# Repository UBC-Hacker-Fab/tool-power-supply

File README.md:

# Tool power supply

A general-purpose power supply board for HackerFab tools. Rev 1 targets the **spin coater** (A2212 930KV BLDC through an EMAX ESC) and the **tube furnace** (up to about 1000 W, switched by an off-board Fotek SSR-60 DA), and also gives general 12 V / 5 V / 3.3 V taps for future tools. A Raspberry Pi Pico 2 monitors and controls it.

Status: **rev 1 schematic done, PCB layout restarted at 90 x 160 mm (120 x 80 mm did not fit); a placement is in the project PCB (first pass scripted, see `tools/pcb_placement/`; the CAN, expander, M3 hole and XT60 changes were laid out by a targeted update on 2026-10-24 that keeps the hand edits; the layout was then finished by hand on 2026-10-25) and routed on 2026-10-26 (hand-planned scripts, no autorouter; KiCad DRC: 0 unconnected, 0 parity issues, only silkscreen items left).** Nothing has been fabricated. Several numbers (creepage, thermal, ESC behavior) are from memory or summaries and are flagged as unverified in the design docs; check them before ordering boards.

Spec source: the Notion page "Power Board Spec Sheet" (HackerFab Central / Electrical): https://app.notion.com/p/38d37907206980e6a0a9c241ee033941. Fab and assembly are planned through JLC (LCSC part numbers in the BOM); through-hole parts are hand-soldered and can come from Digikey or Mouser.

## What the board does

- **120 VAC in** (barrier strip, L / N / PE) splits into two fused branches: a 3 A time-lag branch into the on-board **Mean Well IRM-90-12** (12 V, 6.7 A, 80 W), and a 10 A fast-blow branch through an ACS712 current sensor to the **AC out** barrier strip. An external SSR in the heater's hot lead switches the furnace.
- **12 V bus** (module output) with a 5 mOhm INA226 monitor, an SMCJ15A TVS and a 100 uF bulk cap. There is **no 24 V bus** and no diode between the module and the bus.
- **12 V outputs:** two taps (3 A blade fuse each) and the ESC branch (7.5 A blade fuse, XT60 female). Each is a fuse, then a high-side AO4407C P-FET switch.
- **5 V and 3.3 V rails:** AP63205 and AP63203 fixed bucks off the 12 V bus, each with an INA226 monitor, then two TPS2553 current-limited taps per rail.
- **Pico 2** plugs into sockets. It reads the three INA226s over I2C, switches every DC tap (default ON, pulled low to turn off), senses whether each tap output is present, reads furnace current and two NTCs, drives the SSR through a 2N7002, and drives a 4-pin PWM fan header. The logic-level SMD parts (expander, sense dividers, pull-ups, SSR drive, VSYS diode) sit on the top side in the pocket under the Pico, between the two 8.5 mm sockets. The Pico 2 ships without headers, so it needs two 1x20 male headers (not yet in the BOM).
- **Power budget:** sized for **one tool at a time** (spin coater worst case about 70 W). It is not enforced in hardware, so the 6.7 A limit should be labeled on the board.

Out of scope for rev 1: the litho tool (it keeps its own supplies), the ESC throttle signal (a separate microcontroller handles it), and the thermocouple interface.

## Repository map

| Path | What it is |
|---|---|
| `design-context/design-decisions.md` | Working memory: every decision with its rationale, open questions, datasheet-derived numbers and sourcing. Start here for "why is it like this". |
| `design-context/bom.md` | Rev 1 BOM (LCSC / Digikey / Mouser part numbers, quantities, JLC vs hand assembly). |
| `design-context/routing.md` | How the board is routed: presets, layer plan, lane bundles, placement changes made for routing, checks and results. |
| `design-context/pin-map.md` | Pico 2 GPIO assignment, tap sense circuits, 12 V switch circuit, INA226 addresses. |
| `design-context/power-tree.md` | Generated power tree with consumption per rail and per tap, module budget by scenario. Regenerate with `python3 tools/power_tree/gen_power_tree.py`. |
| `design-context/block-diagram.svg` | Block diagram (Graphviz source `block-diagram.dot`; Mermaid version in `block-diagram.md`). |
| `design-context/pcb-placement.md` | Board outline, zone plan and placement assumptions for the first-pass PCB. |
| `design-context/footprint-sourcing.md` | Which symbols and footprints come from stock KiCad, the HackerFab library, or need downloading. |
| `tool-power-supply-v1/` | The KiCad 10 project: root sheet plus `mains`, `bus12v`, `rails`, `mcu` sub-sheets. |
| `tools/power_tree/` | Generator for `power-tree.md`: reads the schematic through the kicad-happy `kicad` skill and `power_model.json` (off-board loads and assumptions, each with a source). |
| `tools/routing/` | Hand-planned PCB routing scripts, checker and DRC loop (see its README). |
| `tools/schematic/` | Python generator that wrote the schematic (see "Working on the schematic"). |
| `datasheets/` | Datasheets referenced by the decisions (INA226, TPS2553, ACS712, Pico 2, EMAX ESC, and rejected parts). |

## Reviewing the design

1. Read the block diagram above, then the "Decided" sections of `design-context/design-decisions.md`.
2. Open `tool-power-supply-v1/tool-power-supply-v1.kicad_pro` in **KiCad 10**. The schematic is hierarchical: the root sheet shows four sheet symbols joined by sheet pins and bus groups (`I2C`, `EN`, `SENSE`, `FAULT`, `FAN`), and the sheets are wired functional blocks with power symbols and no global labels.
3. Symbols and footprints come from the stock KiCad libraries plus the HackerFab libraries (`hackerfab-kicadlibs`, https://github.com/UBC-Hacker-Fab). A few parts (TPS2553, the 3AG and blade fuses with their clip/holder footprints, barrier strip, IRM-90-12) are only in the HackerFab library, so clone that repo and add its libraries to KiCad before opening the project.
4. Check the BOM (`design-context/bom.md`) against the schematic and pin map.

Current check results: ERC has 0 errors and 2 expected warnings (the Pico's GND and AGND power-output pins tied to the module's -VO pin). The exported netlist matches the intended pin-to-net table for all 79 nets.

**2026-10-26: Pico GPIO re-pinned for routing** (`design-context/pin-map.md`): the left socket order now matches the order the nets leave toward U8 to U11, Q4 to Q6, U14 and the I2C / fan group, and the seven EN pull-ups sit beside their pins. Edited in `mcu.kicad_sch` and the PCB pad nets only; ERC result is unchanged by the change (it currently lists 4 items: the U12 ~{INT} pin and its misplaced no-connect flag, and the Pico GND / AGND pin-type warnings). `tools/schematic/design.py` still has the old pin map.

## Known gaps and open items

- **PCB: routed 2026-10-26, not yet reviewed in KiCad** (90 x 160 mm, 4-layer JLC economy stack-up: F.Cu / In1 GND / In2 GND / B.Cu; routing method, presets, bundles and checks in `design-context/routing.md`, scripts in `tools/routing/`). Four GND pours (stitched, filled with the DRC engine so the 3.2 mm mains rule holds), 612 tracks, 466 vias; DRC with the project's net classes and schematic parity: 0 unconnected, no clearance / hole / mains violations, 164 silkscreen warnings (silk left for later) and the known U13 footprint-library note. Placement was adjusted a little for routing (Q5, the divider resistors, R36 / R37, the EN pull-ups, F4 / F5 flipped; list in `design-context/routing.md`). Placement history: `design-context/pcb-placement.md` and `tools/pcb_placement/`. Still open on the layout: creepage slots (under the IRM-90-12, around the ACS712 and the mains LED dropper), the star-ground solder jumpers (PE, DC GND, ESC, logic, chassis; default open), silkscreen, and a check of the tight vias (0.5 / 0.3 mm) against the JLC DFM report.
- **Schematic omissions:** X2 cap, test points, a gate clamp for the 12 V P-FETs (check Vgs against the 25 V limit during a TVS clamp), and the AO4407C uses the stock FDS9435A symbol. The 120 VAC 3AG fuses (F1, F2) are one symbol each with a custom two-clip footprint (34.21 mm between the clips, from the Littelfuse datasheet); the DC blade fuses (F4, F5, F6) are one symbol each with the Keystone 3557 holder as the footprint, so there are no separate clip or holder symbols.
- **Unverified assumptions:** the ESC's regen behavior (the IRM-90-12 latches off above 12.6 to 16.2 V and needs a power cycle; the design relies on ESC Brake OFF and a ramped throttle), the ESC's own input capacitance (the 100 uF bulk cap assumes the ESC has some), the Fotek SSR's real ratings, creepage numbers (now derived from IEC 60664-1 in `design-guides/`, still to be confirmed), and the Noctua fan's PWM and tach levels. The EMAX manual in `datasheets/` is for the NANO series, not the Simon series in use.
- **Decided 2026-10-21 (design review); in the schematic since 2026-10-22 and in the PCB (placement only) since 2026-10-24:** the board becomes a CAN peripheral of the control board (a second Pico 2 on USB to a lab computer, powered from this board's 5 V). The Pico 2 stays and uses the can2040 PIO CAN library with an SN65HVD230 transceiver; a TCA9534 8-bit I2C expander takes the 7 sense inputs (25 of 26 GPIO becomes 20); mounting holes become floating M3 plated holes with ring vias; the ESC XT60 becomes a vertical female (XT60PB-F, C19268038). New parts: U12 TCA9534PWR (C783615; first drawn as a 16-bit PCA9535C, swapped by the user 2026-10-24 because only 8 inputs are used), U14 SN65HVD230, J10 link connector (5 V, CANH, GND, CANL; replaces J9), R41 + SJ4 termination. Future note: the control board should fall back to USB power if the power board fails. Details in `design-context/design-decisions.md`.
- **Not yet sourced:** M2 hardware and standoffs, the SSR heat sink and wiring, and the DNP dump-load footprint.
- Prices and stock figures date from 2026-10-11 to 2026-10-14. Re-check before ordering.

## Working on the schematic

The schematic was generated from Python tables, and `tools/schematic/design.py` is the source of truth for components and nets.

```sh
python3 tools/schematic/build2.py   # regenerate tool-power-supply-v1/*.kicad_sch
```

It needs KiCad 10 installed at `/Applications/KiCad/KiCad.app` and `hackerfab-kicadlibs` cloned at `~/Documents/Github/hackerfab-kicadlibs`. **Regenerating overwrites any edits made in KiCad.** The schematic is now being edited by hand, so do not rerun the generator unless you have agreed to throw those edits away (it refuses to run while KiCad's `~*.lck` file exists); `design.py` can drift from the `.kicad_sch` files. `tools/schematic/README.md` has details.

## Power tree

`design-context/power-tree.md` is generated from the schematic, so rerun `python3 tools/power_tree/gen_power_tree.py` after any schematic or load change (`--check` reports whether the committed file is stale). It needs Python 3.10+ and the kicad-happy `kicad` skill (default `~/.claude/skills/kicad`, override with `KICAD_HAPPY_SKILL`). Tap and overhead currents live in `tools/power_tree/power_model.json`; the generator fails if a ref in that file no longer matches the schematic. Headline result today: the spin-coater case draws about 5.9 A of the module's 6.7 A, and loading every tap at once exceeds the module, as expected for a one-tool-at-a-time design.

## Keeping this README current

This file is the first point of contact, so it must match the design. When a decision, the architecture, the BOM, the schematic status or the open items change, update the relevant section here in the same change, alongside `design-context/design-decisions.md` (which holds the detail and history).

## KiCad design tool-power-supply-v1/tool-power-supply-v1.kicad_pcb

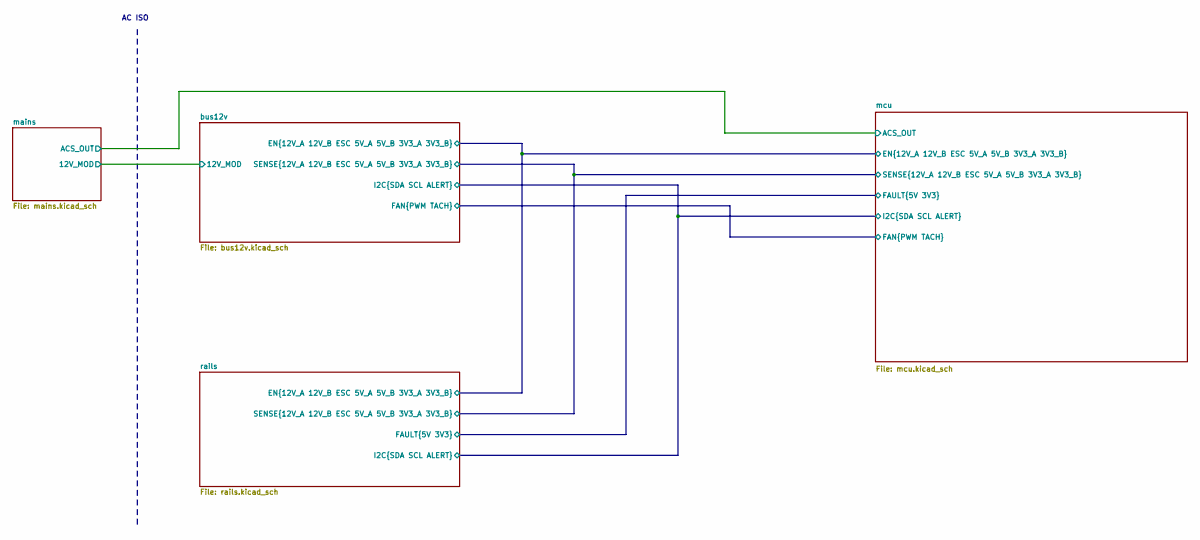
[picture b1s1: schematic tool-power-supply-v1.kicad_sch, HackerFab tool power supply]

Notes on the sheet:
AC ISO

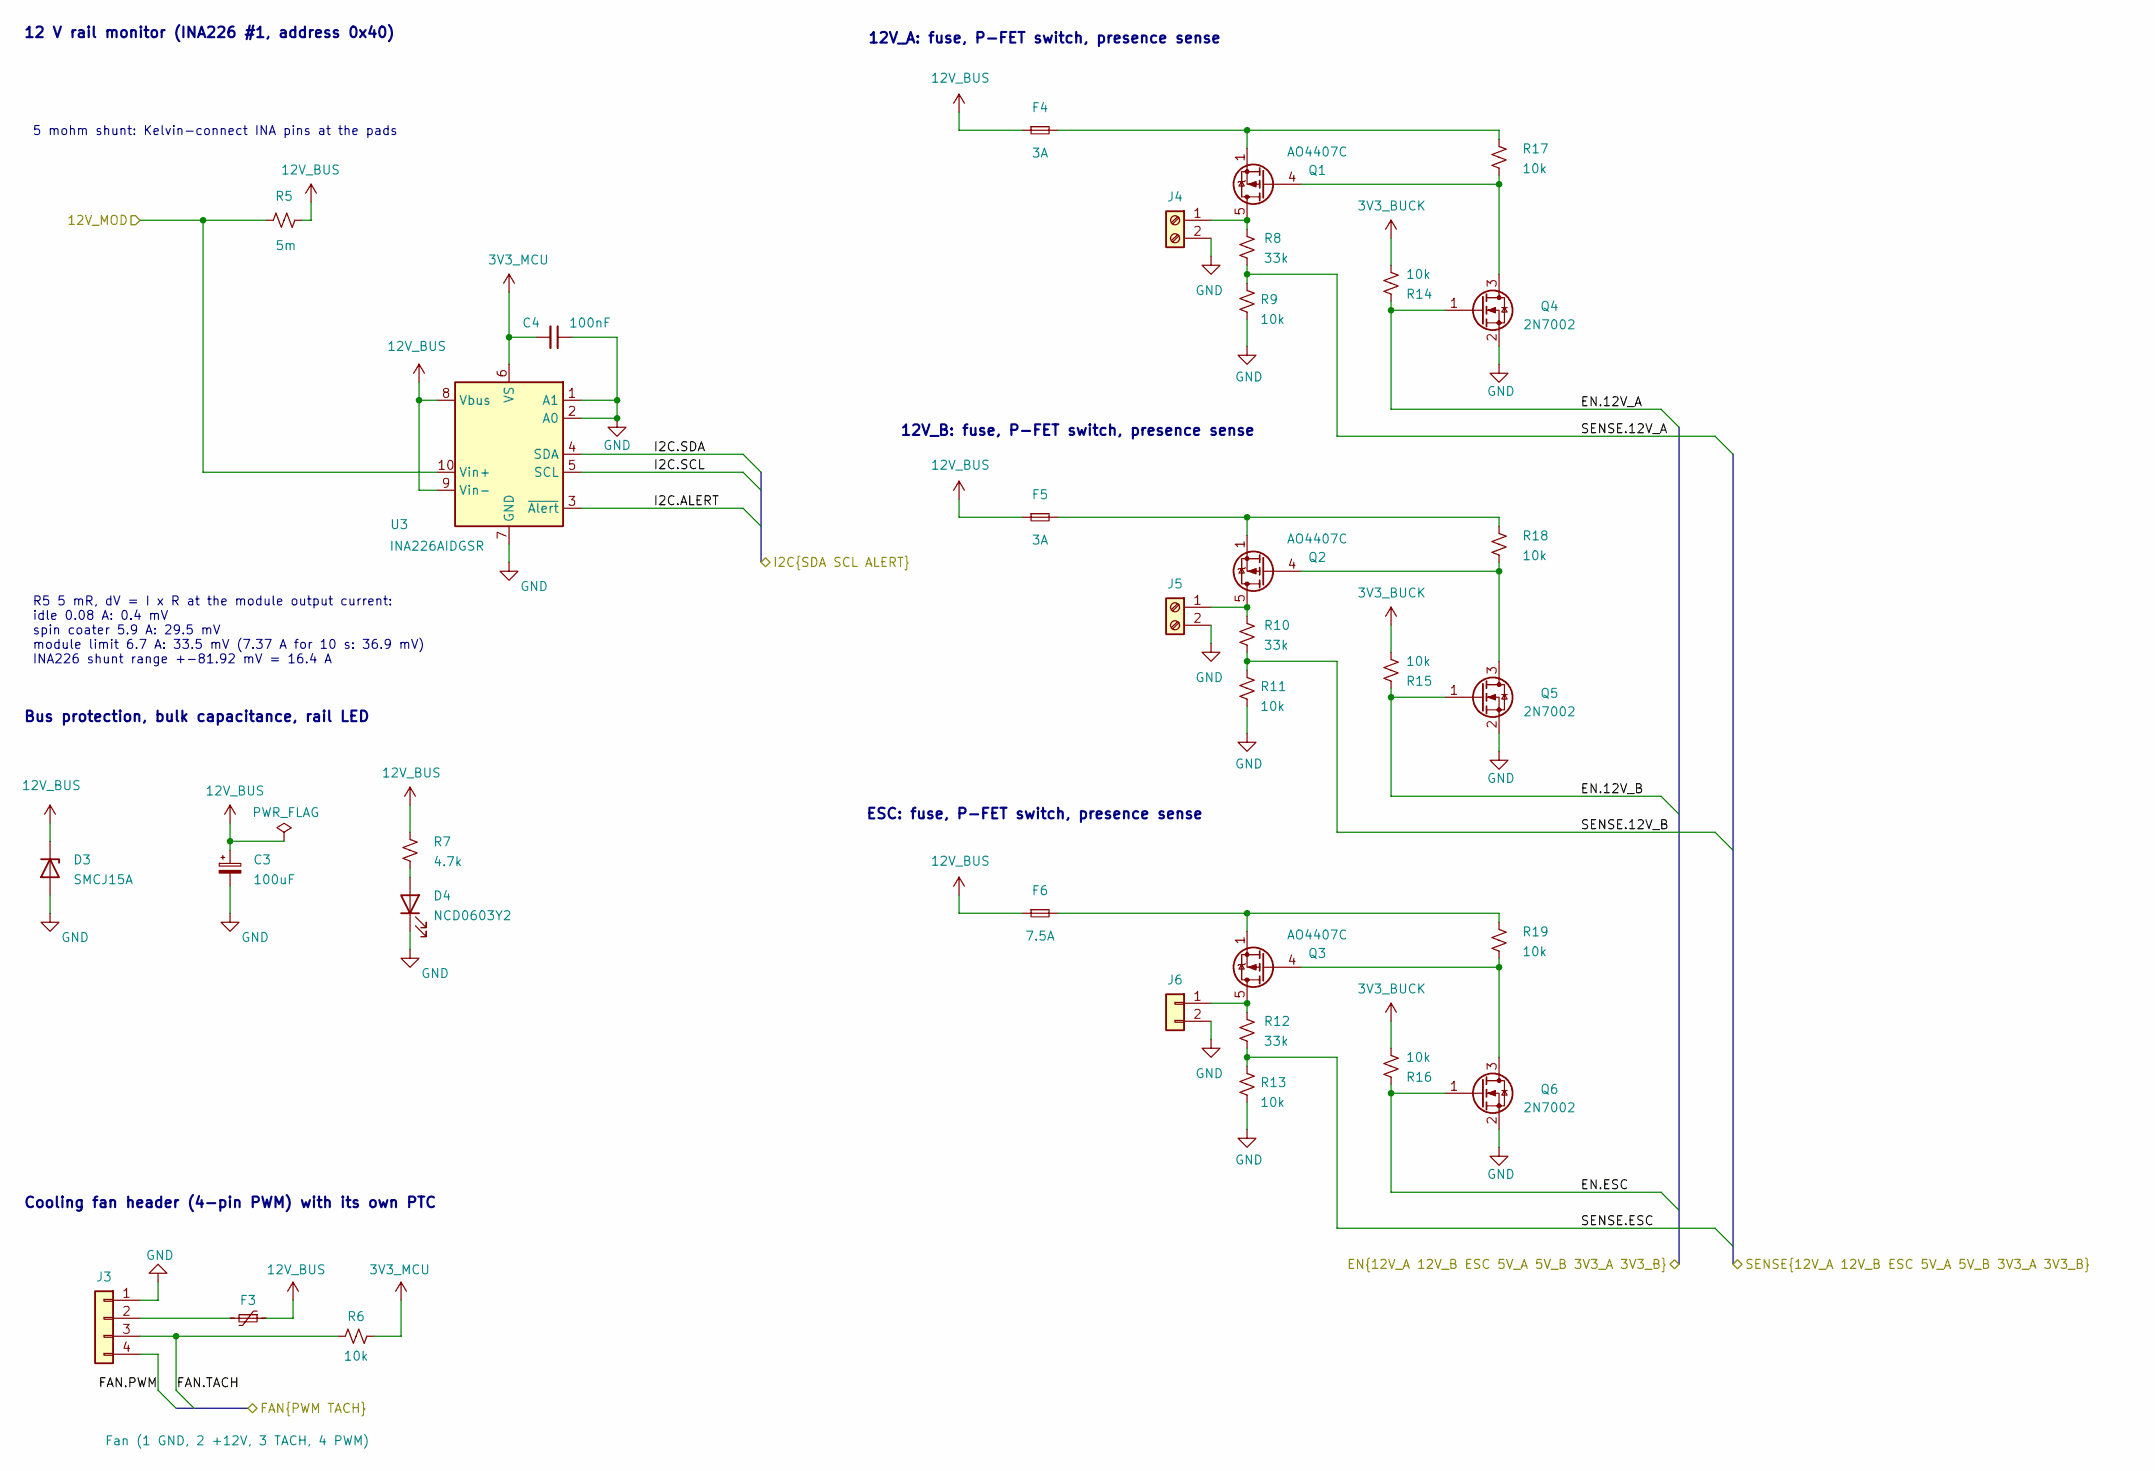
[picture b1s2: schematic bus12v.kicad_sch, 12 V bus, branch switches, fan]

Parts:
C3: 100uF; CP_Elec_6.3x7.7; Voltage 35V; MPN RVE100UF35V67RV0072; LCSC C2836437
C4: 100nF; C_0603_1608Metric; Voltage 50V; MPN CC0603KRX7R9BB104; LCSC C14663
D3: SMCJ15A; D_SMC; MPN SMCJ15A; LCSC C42371550
D4: NCD0603Y2; LED_0603_1608Metric; MPN NCD0603Y2; LCSC C89811
F3: 500mA; Fuse_1206_3216Metric; MPN nSMD050-33V; LCSC C70077
F4, F5: 3A; Fuse_Blade_Keystone_3557-20_P13.47mm; MPN 0ATO003.V (Digikey F5040-ND)
F6: 7.5A; Fuse_Blade_Keystone_3557-20_P13.47mm; MPN 0ATO07.5V (Digikey F11167-ND)
J3: Fan (1 GND, 2 +12V, 3 TACH, 4 PWM); Molex_KK-254_AE-6410-04A_1x04_P2.54mm_Vertical; MPN 47053-1000; Mouser 538-47053-1000
J4, J5: DB128V-5.08-2P-GN-S; TerminalBlock_CUI_TB007-508-02_1x02_P5.08mm_Horizontal; MPN DB128V-5.08-2P-GN-S; LCSC C2915639
J6: XT60PW-F; AMASS_XT60PW-F_1x02_P7.20mm_Horizontal; MPN XT60PW-F; LCSC C428722
Q1, Q2, Q3: AO4407C; SOIC-8_3.9x4.9mm_P1.27mm; MPN AO4407C; LCSC C469397
Q4, Q5, Q6: 2N7002; SOT-23; MPN 2N7002; LCSC C8545
R5: 5m; R_2512_6332Metric; Tolerance 1%; MPN RLP25FEGMR005; LCSC C393074
R6, R9, R11, R13, R14, R15, R16, R17, R18, R19: 10k; R_0603_1608Metric; Tolerance 1%; MPN 0603WAF1002T5E; LCSC C25804
R7: 4.7k; R_0603_1608Metric; Tolerance 1%; MPN 0603WAF4701T5E; LCSC C23162
R8, R10, R12: 33k; R_0603_1608Metric; Tolerance 1%; MPN 0603WAF3302T5E; LCSC C4216
U3: INA226AIDGSR; MSOP-10_3x3mm_P0.5mm; MPN INA226AIDGSR; LCSC C49851

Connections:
3V3_MCU: C4.1, R6.2, U3.6 (VS); also elsewhere on the board
12V_BUS: C3.1, D3.1 (K), F3.1, F4.1, F5.1, F6.1, R5.2, R7.1, U3.8 (Vbus), U3.9 (Vin-); also elsewhere on the board
/bus12v/12V_MOD: R5.1, U3.10 (Vin+); also elsewhere on the board
/bus12v/EN.12V_A: Q4.1 (G), R14.1; also elsewhere on the board
/bus12v/EN.12V_B: Q5.1 (G), R15.1; also elsewhere on the board
/bus12v/EN.ESC: Q6.1 (G), R16.1; also elsewhere on the board
/bus12v/FAN.PWM: J3.4; also elsewhere on the board
/bus12v/FAN.TACH: J3.3, R6.1; also elsewhere on the board
/bus12v/I2C.ALERT: U3.3 (~Alert); also elsewhere on the board
/bus12v/I2C.SCL: U3.5 (SCL); also elsewhere on the board
/bus12v/I2C.SDA: U3.4 (SDA); also elsewhere on the board
/bus12v/SENSE.12V_A: R8.2, R9.1; also elsewhere on the board
/bus12v/SENSE.12V_B: R10.2, R11.1; also elsewhere on the board
/bus12v/SENSE.ESC: R12.2, R13.1; also elsewhere on the board
GND: C3.2, C4.2, D3.2 (A), D4.1 (K), J3.1, J4.2, J5.2, J6.2 (-), Q4.2 (S), Q5.2 (S), Q6.2 (S), R9.2, R11.2, R13.2, U3.1 (A1), U3.2 (A0), U3.7 (GND); also elsewhere on the board
unnamed: D4.2 (A), R7.2
unnamed: F4.2, Q1.1 (S), Q1.2 (S), Q1.3 (S), R17.1
unnamed: F5.2, Q2.1 (S), Q2.2 (S), Q2.3 (S), R18.1
unnamed: F6.2, Q3.1 (S), Q3.2 (S), Q3.3 (S), R19.1
unnamed: F3.2, J3.2
unnamed: J4.1, Q1.5 (D), Q1.6 (D), Q1.7 (D), Q1.8 (D), R8.1
unnamed: J5.1, Q2.5 (D), Q2.6 (D), Q2.7 (D), Q2.8 (D), R10.1
unnamed: J6.1 (+), Q3.5 (D), Q3.6 (D), Q3.7 (D), Q3.8 (D), R12.1
unnamed: Q1.4 (G), Q4.3 (D), R17.2
unnamed: Q2.4 (G), Q5.3 (D), R18.2
unnamed: Q3.4 (G), Q6.3 (D), R19.2

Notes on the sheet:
ESC: fuse, P-FET switch, presence sense
Cooling fan header (4-pin PWM) with its own PTC
Bus protection, bulk capacitance, rail LED
12 V rail monitor (INA226 #1, address 0x40)
12V_A: fuse, P-FET switch, presence sense
R5 5 mR, dV = I x R at the module output current: idle 0.08 A: 0.4 mV spin coater 5.9 A: 29.5 mV module limit 6.7 A: 33.5 mV (7.37 A for 10 s: 36.9 mV) INA226 shunt range +-81.92 mV = 16.4 A
5 mohm shunt: Kelvin-connect INA pins at the pads
12V_B: fuse, P-FET switch, presence sense

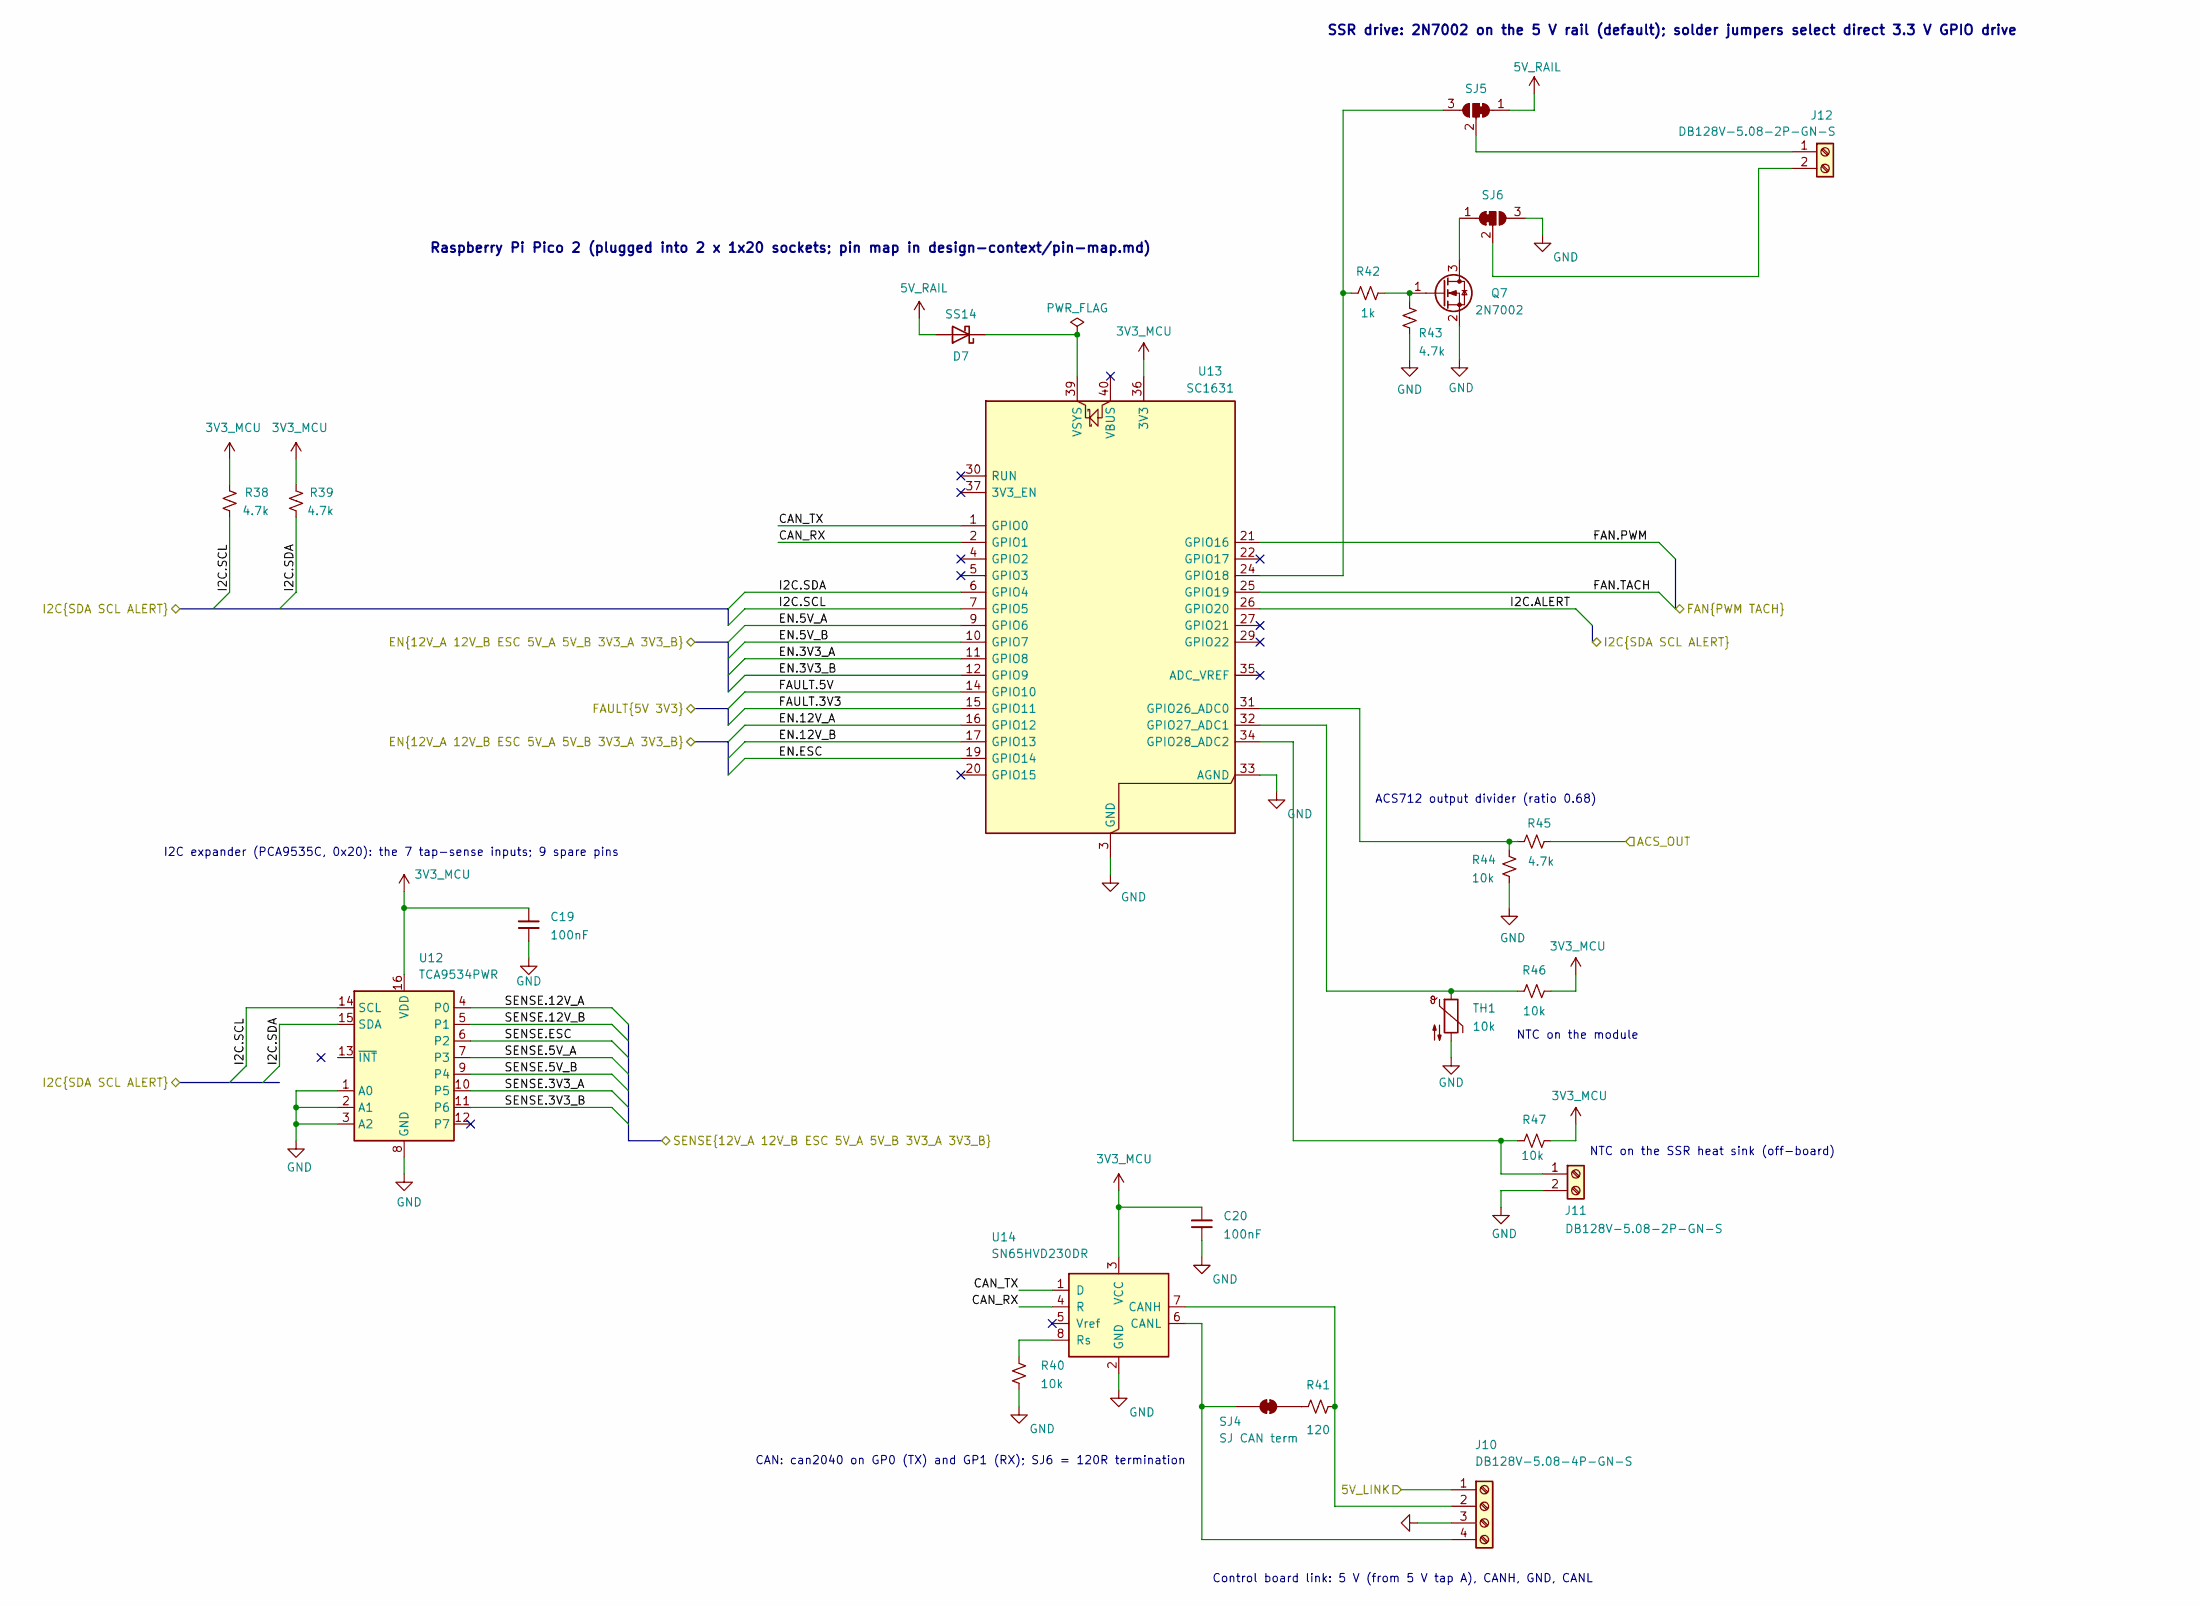
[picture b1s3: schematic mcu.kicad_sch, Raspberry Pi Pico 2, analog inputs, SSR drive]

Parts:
C19, C20: 100nF; C_0603_1608Metric; Voltage 50V; MPN CC0603KRX7R9BB104; LCSC C14663
D7: SS14; D_SMA; MPN SS14; LCSC C2480
J10: DB128V-5.08-4P-GN-S; TerminalBlock_CUI_TB007-508-04_1x04_P5.08mm_Horizontal; MPN DB128V-5.08-4P-GN-S; LCSC C2915641
J11, J12: DB128V-5.08-2P-GN-S; TerminalBlock_CUI_TB007-508-02_1x02_P5.08mm_Horizontal; MPN DB128V-5.08-2P-GN-S; LCSC C2915639
Q7: 2N7002; SOT-23; MPN 2N7002; LCSC C8545
R38, R39, R43, R45: 4.7k; R_0603_1608Metric; Tolerance 1%; MPN 0603WAF4701T5E; LCSC C23162
R40, R44, R46, R47: 10k; R_0603_1608Metric; Tolerance 1%; MPN 0603WAF1002T5E; LCSC C25804
R41: 120; R_0603_1608Metric; Tolerance 1%; MPN 0603WAF1200T5E; LCSC C22787
R42: 1k; R_0603_1608Metric; Tolerance 1%; MPN 0603WAF1001T5E; LCSC C21190
SJ4: SJ CAN term; SolderJumper-2_P1.3mm_Bridged_RoundedPad1.0x1.5mm
SJ5: SJ SSR+ (1-2 = 5V, 2-3 = GPIO); SolderJumper-3_P1.3mm_Bridged12_RoundedPad1.0x1.5mm
SJ6: SJ SSR- (1-2 = MOSFET, 2-3 = GND); SolderJumper-3_P1.3mm_Bridged12_RoundedPad1.0x1.5mm
TH1: 10k; R_0603_1608Metric; MPN NCP18XH103F03RB; LCSC C13564
U12: TCA9534PWR; TSSOP-16_4.4x5mm_P0.65mm; MPN TCA9534PWR; LCSC C783615
U13: SC1631; RaspberryPi_Pico_Common_THT; MPN SC1631; LCSC C41407547
U14: SN65HVD230DR; SOIC-8_3.9x4.9mm_P1.27mm; MPN SN65HVD230DR; LCSC C12084

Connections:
3V3_MCU: C19.1, C20.1, R38.2, R39.2, R46.1, R47.1, U12.16 (VDD), U13.36 (3V3), U14.3 (VCC); also elsewhere on the board
5V_RAIL: D7.2 (A), SJ5.1 (A); also elsewhere on the board
/bus12v/EN.3V3_A: U13.14 (GPIO10); also elsewhere on the board
/bus12v/EN.3V3_B: U13.19 (GPIO14); also elsewhere on the board
/bus12v/EN.5V_A: U13.4 (GPIO2); also elsewhere on the board
/bus12v/EN.5V_B: U13.12 (GPIO9); also elsewhere on the board
/bus12v/EN.12V_A: U13.10 (GPIO7); also elsewhere on the board
/bus12v/EN.12V_B: U13.11 (GPIO8); also elsewhere on the board
/bus12v/EN.ESC: U13.16 (GPIO12); also elsewhere on the board
/bus12v/FAN.PWM: U13.17 (GPIO13); also elsewhere on the board
/bus12v/FAN.TACH: U13.20 (GPIO15); also elsewhere on the board
/bus12v/I2C.ALERT: U13.9 (GPIO6); also elsewhere on the board
/bus12v/I2C.SCL: R38.1, U12.14 (SCL), U13.7 (GPIO5); also elsewhere on the board
/bus12v/I2C.SDA: R39.1, U12.15 (SDA), U13.6 (GPIO4); also elsewhere on the board
/bus12v/SENSE.3V3_A: U12.10 (P5); also elsewhere on the board
/bus12v/SENSE.3V3_B: U12.11 (P6); also elsewhere on the board
/bus12v/SENSE.5V_A: U12.7 (P3); also elsewhere on the board
/bus12v/SENSE.5V_B: U12.9 (P4); also elsewhere on the board
/bus12v/SENSE.12V_A: U12.4 (P0); also elsewhere on the board
/bus12v/SENSE.12V_B: U12.5 (P1); also elsewhere on the board
/bus12v/SENSE.ESC: U12.6 (P2); also elsewhere on the board
/mains/ACS_OUT: R45.1; also elsewhere on the board
/mcu/5V_LINK: J10.1; also elsewhere on the board
/mcu/CAN_RX: U13.2 (GPIO1), U14.4 (R)
/mcu/CAN_TX: U13.1 (GPIO0), U14.1 (D)
/mcu/FAULT.3V3: U13.15 (GPIO11); also elsewhere on the board
/mcu/FAULT.5V: U13.5 (GPIO3); also elsewhere on the board
GND: C19.2, C20.2, J10.3, J11.2, Q7.2 (S), R40.2, R43.2, R44.2, SJ6.3 (B), TH1.2, U12.1 (A0), U12.2 (A1), U12.3 (A2), U12.8 (GND), U13.3 (GND), U13.8 (GND), U13.13 (GND), U13.18 (GND), U13.23 (GND), U13.28 (GND), U13.33 (AGND), U13.38 (GND), U14.2 (GND); also elsewhere on the board
unnamed: D7.1 (K), U13.39 (VSYS)
unnamed: J10.2, R41.2, U14.7 (CANH)
unnamed: J10.4, SJ4.1 (A), U14.6 (CANL)
unnamed: J11.1, R47.2, U13.34 (GPIO28_ADC2)
unnamed: J12.1, SJ5.2 (C)
unnamed: J12.2, SJ6.2 (C)
unnamed: Q7.3 (D), SJ6.1 (A)
unnamed: Q7.1 (G), R42.2, R43.1
unnamed: R41.1, SJ4.2 (B)
unnamed: R42.1, SJ5.3 (B), U13.24 (GPIO18)
unnamed: R44.1, R45.2, U13.31 (GPIO26_ADC0)
unnamed: R46.2, TH1.1, U13.32 (GPIO27_ADC1)
unnamed: R40.1, U14.8 (Rs)

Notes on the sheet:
NTC on the SSR heat sink (off-board)
ACS712 output divider (ratio 0.68)
Raspberry Pi Pico 2 (plugged into 2 x 1x20 sockets; pin map in design-context/pin-map.md)
NTC on the module
CAN: can2040 on GP0 (TX) and GP1 (RX); SJ6 = 120R termination
SSR drive: 2N7002 on the 5 V rail (default); solder jumpers select direct 3.3 V GPIO drive
Control board link: 5 V (from 5 V tap A), CANH, GND, CANL
I2C expander (PCA9535C, 0x20): the 7 tap-sense inputs; 9 spare pins

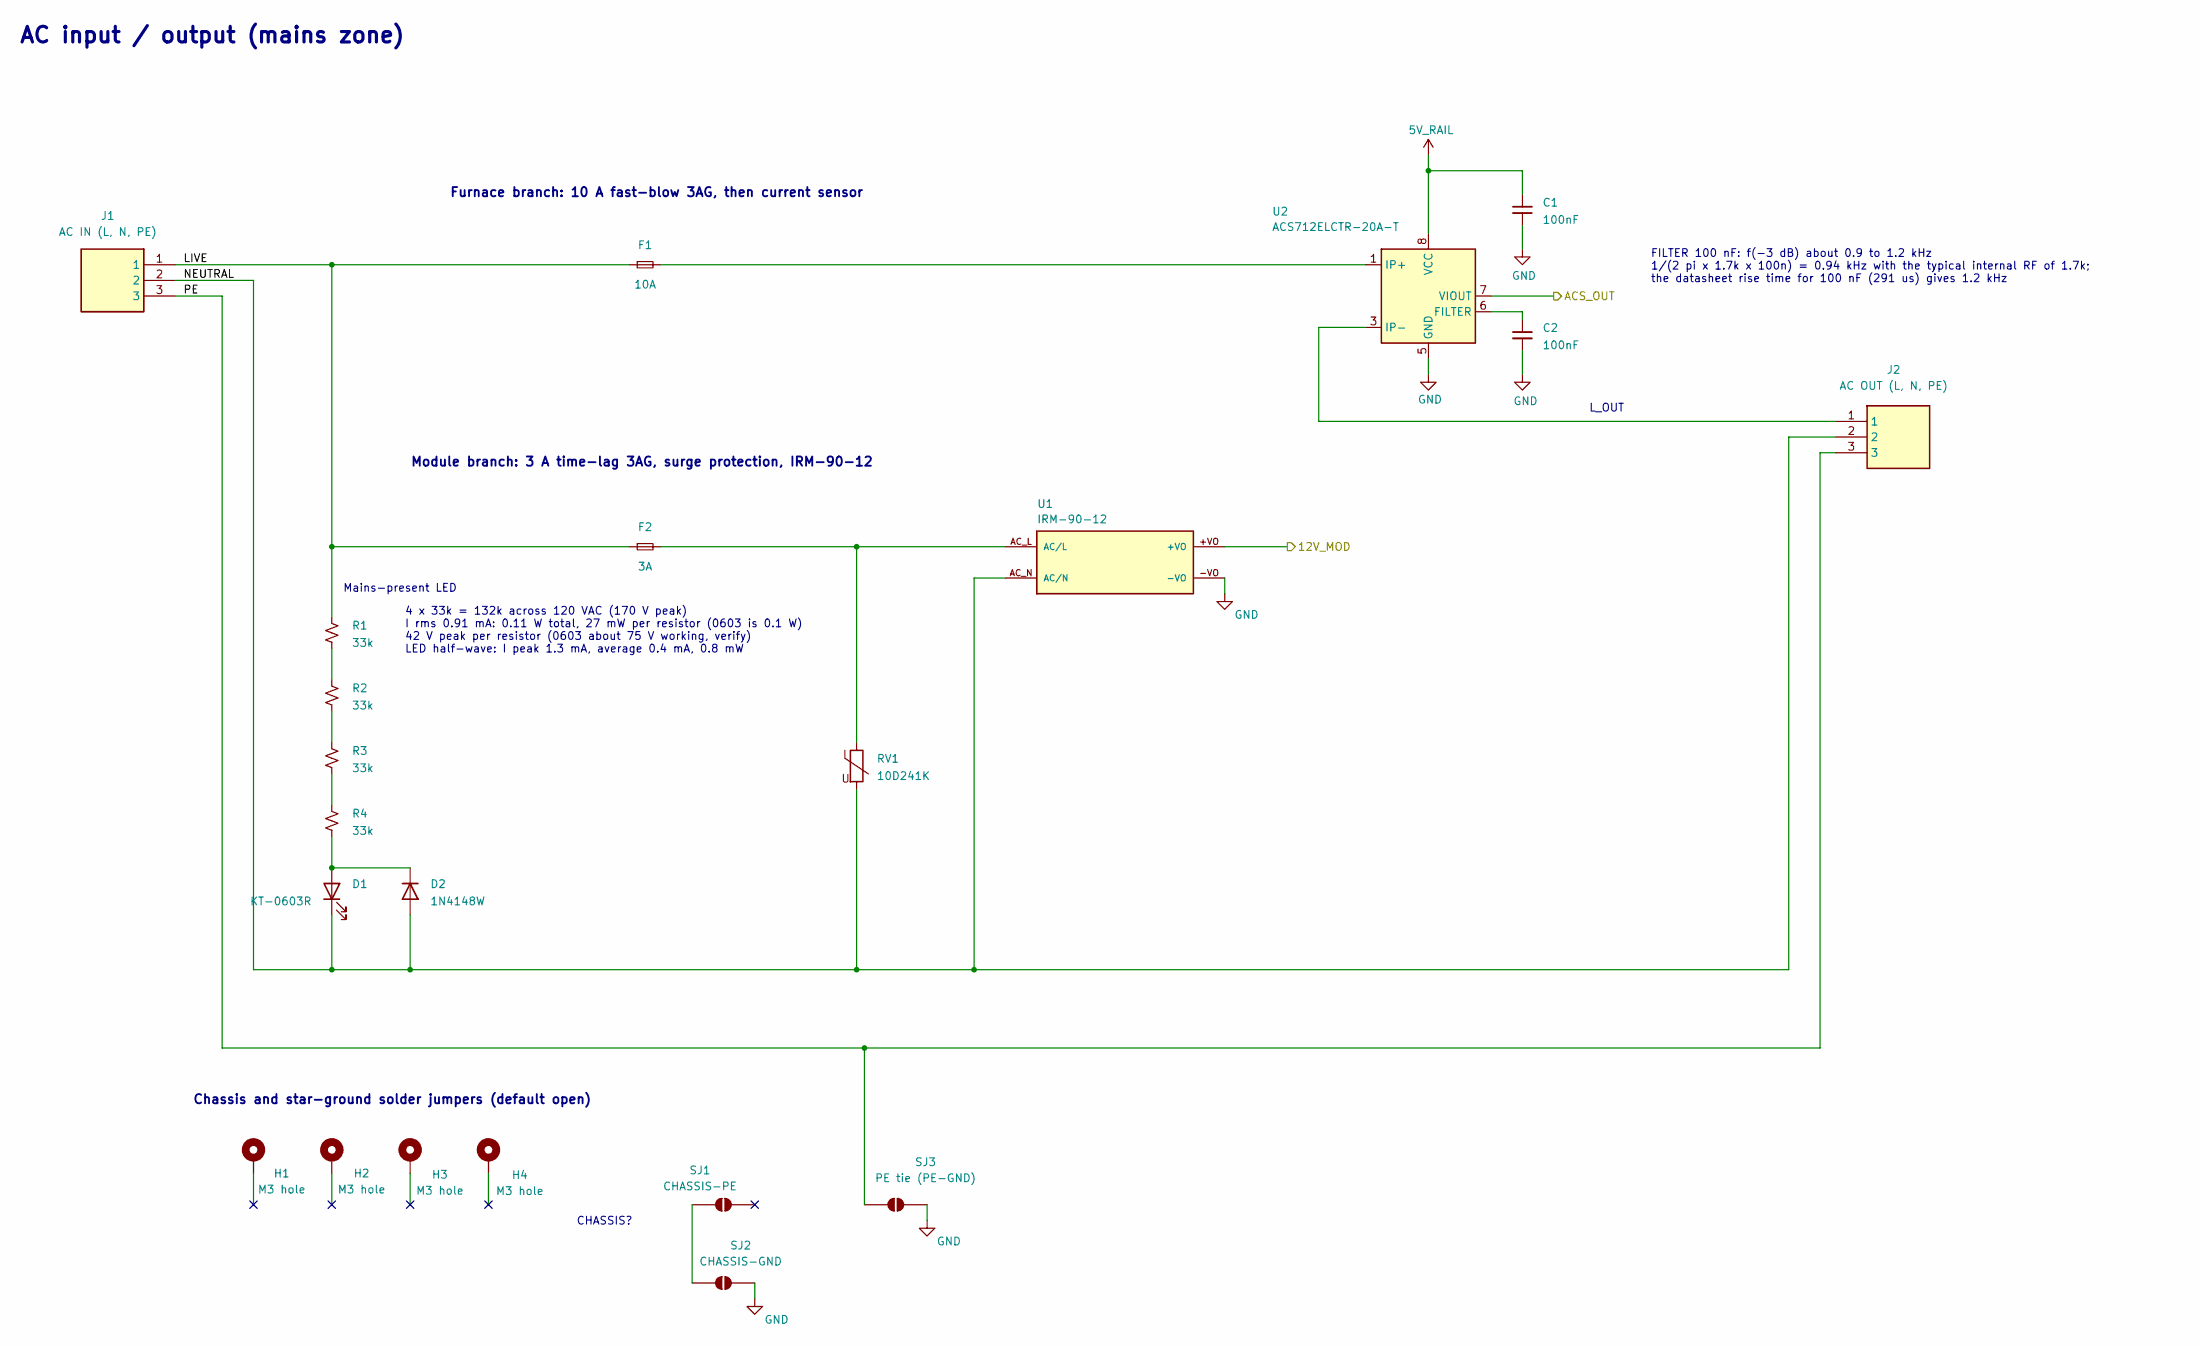
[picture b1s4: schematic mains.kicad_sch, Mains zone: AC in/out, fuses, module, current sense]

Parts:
C1, C2: 100nF; C_0603_1608Metric; Voltage 50V; MPN CC0603KRX7R9BB104; LCSC C14663
D1: KT-0603R; LED_0603_1608Metric; MPN KT-0603R; LCSC C2286
D2: 1N4148W; D_SOD-123; MPN 1N4148W; LCSC C81598
F1: 10A; Fuse_3AG_6.3x32mm_Clips_Littelfuse_102_122_P34.21mm; MPN 0314010.HXP (Digikey F3222-ND)
F2: 3A; Fuse_3AG_6.3x32mm_Clips_Littelfuse_102_122_P34.21mm; MPN 0313003.HXP (Digikey F2545-ND; 4A 03130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
H1, H2, H3, H4: M3 hole; MountingHole_3.2mm_M3_Pad_Via
J1: AC IN (L, N, PE); TerminalBlock_Ningbo-Kagnex_HB9500M_1x03_P9.5mm; MPN HB9500M-9.5-03P-13-00A; LCSC C162697
J2: AC OUT (L, N, PE); TerminalBlock_Ningbo-Kagnex_HB9500M_1x03_P9.5mm; MPN HB9500M-9.5-03P-13-00A; LCSC C162697
R1, R2, R3, R4: 33k; R_0603_1608Metric; Tolerance 1%; MPN 0603WAF3302T5E; LCSC C4216
RV1: 10D241K; RV_Disc_D12mm_W5.4mm_P7.5mm; MPN 10D241K; LCSC C49072899
SJ1: CHASSIS-PE; SolderJumper-2_P1.3mm_Open_RoundedPad1.0x1.5mm
SJ2: CHASSIS-GND; SolderJumper-2_P1.3mm_Open_RoundedPad1.0x1.5mm
SJ3: PE tie (PE-GND); SolderJumper-2_P1.3mm_Open_RoundedPad1.0x1.5mm
U1: IRM-90-12; CONV_IRM-90-12; MPN IRM-90-12; LCSC C6577385
U2: ACS712ELCTR-20A-T; SOIC-8_3.9x4.9mm_P1.27mm; MPN ACS712ELCTR-20A-T; LCSC C10681

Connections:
5V_RAIL: C1.1, U2.8 (VCC); also elsewhere on the board
/bus12v/12V_MOD: U1.+VO; also elsewhere on the board
/mains/ACS_OUT: U2.7 (VIOUT); also elsewhere on the board
/mains/LIVE: F1.1, F2.1, J1.1, R1.1
/mains/NEUTRAL: D1.1 (K), D2.2 (A), J1.2, J2.2, RV1.2, U1.AC_N (AC/N)
/mains/PE: J1.3, J2.3, SJ3.1 (A)
GND: C1.2, C2.2, SJ2.2 (B), SJ3.2 (B), U1.-VO, U2.5 (GND); also elsewhere on the board
unnamed: D1.2 (A), D2.1 (K), R4.2
unnamed: F1.2, U2.1 (IP+), U2.2 (IP+)
unnamed: J2.1, U2.3 (IP-), U2.4 (IP-)
unnamed: R1.2, R2.1
unnamed: R2.2, R3.1
unnamed: R3.2, R4.1
unnamed: SJ1.1 (A), SJ2.1 (A)
unnamed: F2.2, RV1.1, U1.AC_L (AC/L)
unnamed: C2.1, U2.6 (FILTER)

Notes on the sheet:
Furnace branch: 10 A fast-blow 3AG, then current sensor
AC input / output (mains zone)
Mains-present LED
FILTER 100 nF: f(-3 dB) about 0.9 to 1.2 kHz 1/(2 pi x 1.7k x 100n) = 0.94 kHz with the typical internal RF of 1.7k; the datasheet rise time for 100 nF (291 us) gives 1.2 kHz
Chassis and star-ground solder jumpers (default open)
4 x 33k = 132k across 120 VAC (170 V peak) I rms 0.91 mA: 0.11 W total, 27 mW per resistor (0603 is 0.1 W) 42 V peak per resistor (0603 about 75 V working, verify) LED half-wave: I peak 1.3 mA, average 0.4 mA, 0.8 mW
L_OUT
Module branch: 3 A time-lag 3AG, surge protection, IRM-90-12
CHASSIS?
